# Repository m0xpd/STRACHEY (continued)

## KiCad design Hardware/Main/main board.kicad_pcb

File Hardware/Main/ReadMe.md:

# Main Board

This folder contains details of STRACHEY's Main Board which you seen below (component side) 

<p width=100%, align="center">

You can download the main board's schematic as a [.sch file](https://github.com/m0xpd/STRACHEY/blob/main/Hardware/Main/main%20board.kicad_sch) into your PCB program (KiCad etc) or see a [PDF version](https://github.com/m0xpd/STRACHEY/blob/main/Hardware/Main/main%20board%20schematic.pdf).

The Main Board hosts power supplies, the Arduino Nano, the DACs, output drivers, input protection and conditioning circuits, the Turing Machine Expansion port, and interface to the control Board.

I am new to KiCad and the BoM generator produces output in .csv format. I have decided to save this information [as an Excel file](https://github.com/m0xpd/STRACHEY/blob/main/Hardware/Main/Strachey%20main%20board%20BoM.xlsx) to retain some edits I made. 

There are a few minor points of potential confusion in the BoM (e.g. where I gave some resistors value "10K" and others "10k"), but I'm sure you'll figure it out. Note particularly that the two multi-turn trimmers, TR1 and TR2  (the blue components seen in the photo above) are listed as having value 1k in the schematic and the BoM. I decided to use 10k components,as I had them to hand. Any value above 1k (and up to 100k) will work fine. There is some description of calibrating the trimmers [here](https://github.com/m0xpd/STRACHEY/tree/main#calibration-and-configuration).

I am grateful to 'Harpooneer' who is building a STRACHEY sequencer - he has pointed out that the Main PCB is too congested around the trimmers TR1 and TR2 and we have discussed the build. TR1 and TR2 should be Bourns 3296W (or equivalent) types. They do just fit (as you see in the image above) but it certainly is a squeeze! I found assembly of the prototype easier if you fit the trimmers before other adjacent componenents (R37, R43, R44 and R45) and ensure that C8 is a slim disc ceramic. 

The [.pcb file](https://github.com/m0xpd/STRACHEY/blob/main/Hardware/Main/main%20board.kicad_pcb) and [.pro file](https://github.com/m0xpd/STRACHEY/blob/main/Hardware/Main/main%20board.kicad_pro) (togther with the [.sch file](https://github.com/m0xpd/STRACHEY/blob/main/Hardware/Main/main%20board.kicad_sch) ) constitute a KiCad project, which define the Main board. 

[JLCPCB](https://jlcpcb.com) made the boards for my prototype and did their usual excellent job (usual disclaimer) - you can see the top and bottom sides of the Main Board below:

There is description of how to configure the expansion port (the 2*8 pin header, JP4, seen at the bottom of the main board) by setting shorting links on JP3 (the 3 pin header, near the middle of the main board) [here](https://github.com/m0xpd/STRACHEY/tree/main#calibration-and-configuration).

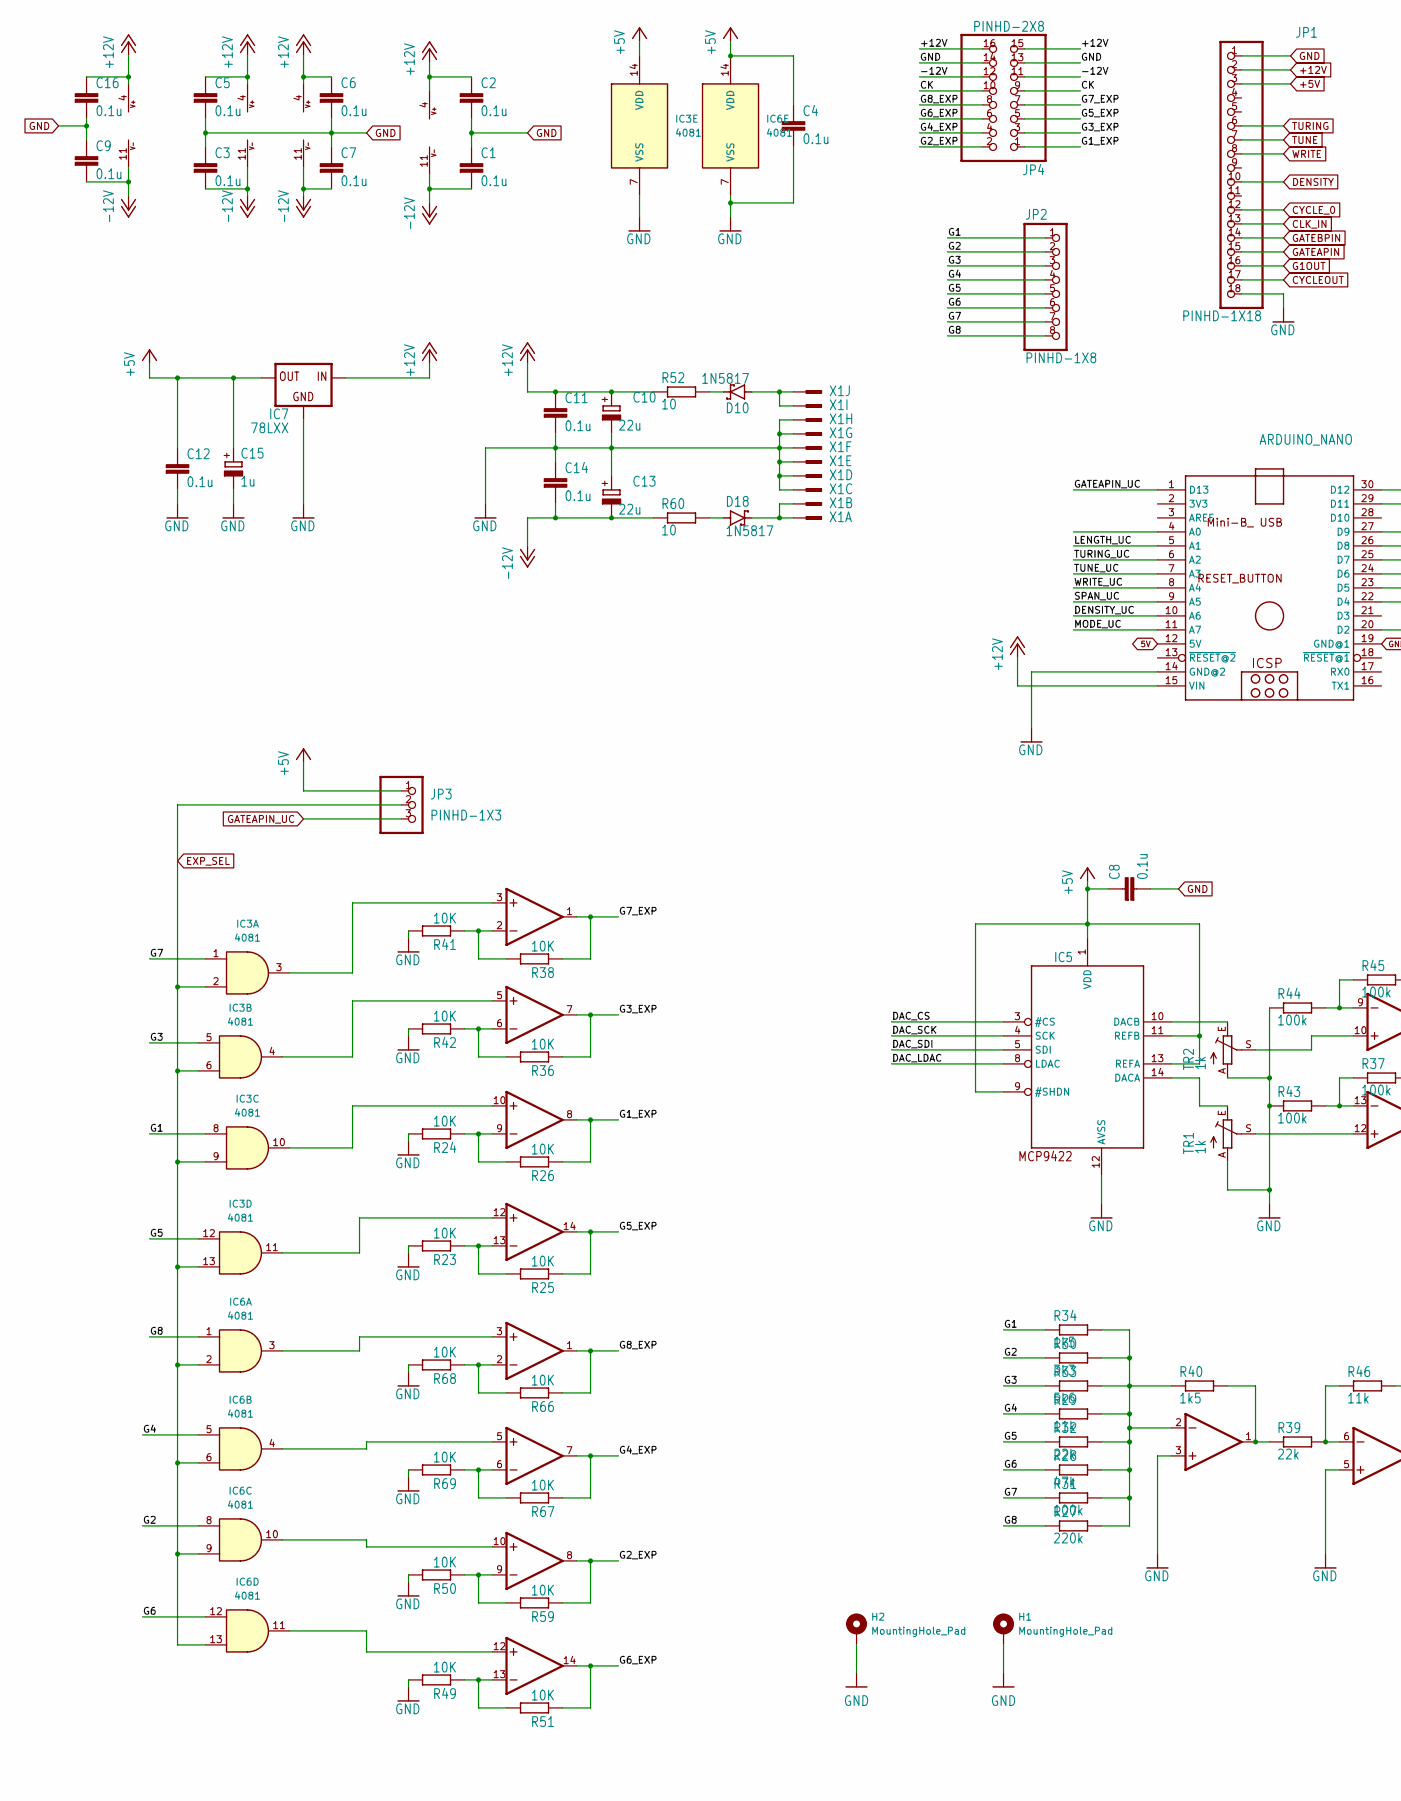
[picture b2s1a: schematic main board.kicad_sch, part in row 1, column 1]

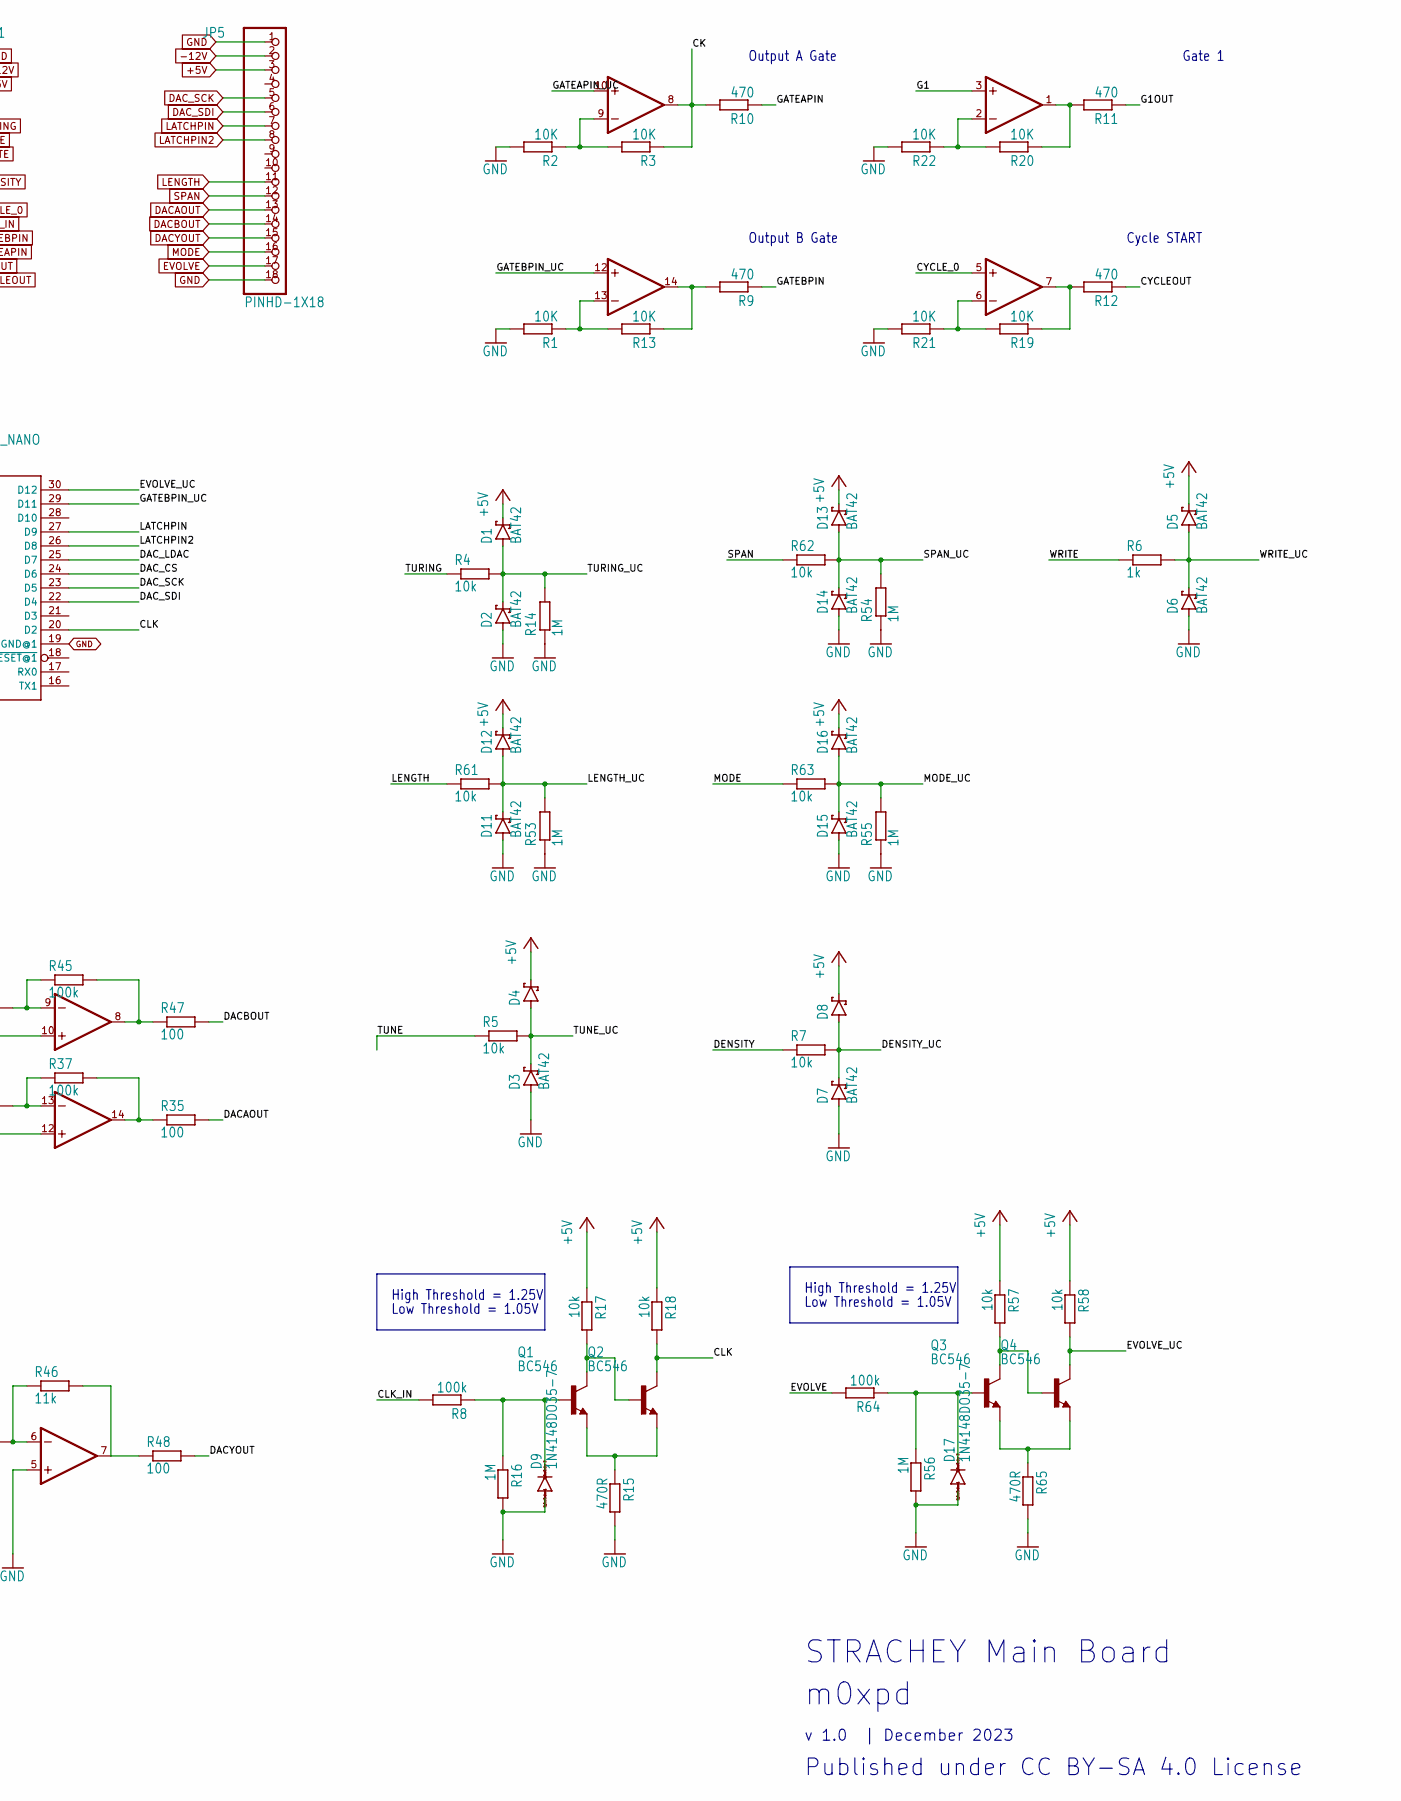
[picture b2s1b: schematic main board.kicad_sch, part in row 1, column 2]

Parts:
C1, C2, C3, C4, C5, C6, C7, C8, C9, C11, C12, C14, C16: 0.1u; C050-025X075
C10, C13: 22u; E2,5-5
C15: 1u; E2,5-5
D1, D2, D3, D4, D5, D6, D7, D8, D11, D12, D13, D14, D15, D16: BAT42; DO35-7
D9, D17: 1N4148DO35-7; DO35-7
D10, D18: 1N5817; DO35-7
H1, H2: MountingHole_Pad; MountingHole_3.2mm_M3_DIN965_Pad_TopBottom
IC1, IC2, IC4, IC8: TL084P; DIL14
IC3, IC6: 4081; DIP-14_W7.62mm_Socket_LongPads
IC5: MCP9422; DIL14
IC7: 78LXX
JP1, JP5: PINHD-1X18; 1X18
JP2: PINHD-1X8; 1X08
JP3: PINHD-1X3; 1X03
JP4: PINHD-2X8; 2X08
Q1, Q2, Q3, Q4: BC546; TO92-EBC
R1, R2, R3, R13, R19, R20, R21, R22, R23, R24, R25, R26, R36, R38, R41, R42, R49, R50, R51, R59, R66, R67, R68, R69: 10K; 0204_7
R4, R5, R7, R17, R18, R57, R58, R61, R62, R63: 10k; 0204_7
R6: 1k; 0204_7
R8, R31, R37, R43, R44, R45, R64: 100k; 0204_7
R9, R10, R11, R12: 470; 0204_7
R14, R16, R53, R54, R55, R56: 1M; 0204_7
R15, R65: 470R; 0204_7
R27: 220k; 0204_7
R28: 47k; 0204_7
R29, R46: 11k; 0204_7
R30: 3k3; 0204_7
R32, R39: 22k; 0204_7
R33: 5k6; 0204_7
R34, R40: 1k5; 0204_7
R35, R47, R48: 100; 0204_7
R52, R60: 10; 0204_7
TR1, TR2: 1k; B64Y
U$1: ARDUINO_NANO
X1: 2510-; PAK100_2500-10

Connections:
5V: U$1.12 (5V)
+5V: C4.1, C8.1, C12.1, C15.+, D1.C, D4.C, D5.C, D8.C, D12.C, D13.C, D16.C, IC3.14 (VDD), IC5.1 (VDD), IC5.9 (#SHDN), IC5.11 (REFB), IC5.13 (REFA), IC6.14 (VDD), IC7.OUT, JP1.3, JP3.1, JP5.3, R17.1, R18.1, R57.1, R58.1
+12V: C2.1, C5.1, C6.1, C10.+, C11.1, C16.1, IC1.4 (V+), IC2.4 (V+), IC4.4 (V+), IC7.IN, IC8.4 (V+), JP1.2, JP4.15, JP4.16, R52.1, U$1.15 (VIN)
-12V: C1.2, C3.2, C7.2, C9.2, C13.-, C14.2, IC1.11 (V-), IC2.11 (V-), IC4.11 (V-), IC8.11 (V-), JP4.11, JP4.12, JP5.2, R60.1
/CK: IC1.8 (OUT), JP4.9, JP4.10, R3.1, R10.2
/CLK: Q2.C, R18.2, U$1.20 (D2)
/DAC_CS: IC5.3 (#CS), U$1.24 (D6)
/DAC_LDAC: IC5.8 (LDAC), U$1.25 (D7)
/DENSITY_UC: D7.C, D8.A, R7.2, U$1.10 (A6)
/EVOLVE_UC: Q4.C, R58.2, U$1.30 (D12)
/G1: IC1.3 (+IN), IC3.8, JP2.1, R34.1
/G1_EXP: IC2.8 (OUT), JP4.1, R26.1
/G2: IC6.8, JP2.2, R30.1
/G2_EXP: IC8.8 (OUT), JP4.2, R59.1
/G3: IC3.5, JP2.3, R33.1
/G3_EXP: IC2.7 (OUT), JP4.3, R36.1
/G4: IC6.5, JP2.4, R29.1
/G4_EXP: IC8.7 (OUT), JP4.4, R67.1
/G5: IC3.12, JP2.5, R32.1
/G5_EXP: IC2.14 (OUT), JP4.5, R25.1
/G6: IC6.12, JP2.6, R28.1
/G6_EXP: IC8.14 (OUT), JP4.6, R51.1
/G7: IC3.1, JP2.7, R31.1
/G7_EXP: IC2.1 (OUT), JP4.7, R38.1
/G8: IC6.1, JP2.8, R27.1
/G8_EXP: IC8.1 (OUT), JP4.8, R66.1
/GATEBPIN_UC: IC1.12 (+IN), U$1.29 (D11)
/LENGTH_UC: D11.C, D12.A, R53.2, R61.2, U$1.5 (A1)
/MODE_UC: D15.C, D16.A, R55.2, R63.2, U$1.11 (A7)
/SPAN_UC: D13.A, D14.C, R54.2, R62.2, U$1.9 (A5)
/TUNE_UC: D3.C, D4.A, R5.2, U$1.7 (A3)
/TURING_UC: D1.A, D2.C, R4.2, R14.2, U$1.6 (A2)
/WRITE_UC: D5.A, D6.C, R6.2, U$1.8 (A4)
CLK_IN: JP1.13, R8.2
CYCLEOUT: JP1.17, R12.1
CYCLE_0: IC1.5 (+IN), JP1.12
DACAOUT: JP5.13, R35.2
DACBOUT: JP5.14, R47.2
DACYOUT: JP5.15, R48.2
DAC_SCK: IC5.4 (SCK), JP5.5, U$1.23 (D5)
DAC_SDI: IC5.5 (SDI), JP5.6, U$1.22 (D4)
DENSITY: JP1.10, R7.1
EVOLVE: JP5.17, R64.2
EXP_SEL: IC3.2, IC3.6, IC3.9, IC3.13, IC6.2, IC6.6, IC6.9, IC6.13, JP3.2
G1OUT: JP1.16, R11.1
GATEAPIN: JP1.15, R10.1
GATEAPIN_UC: IC1.10 (+IN), JP3.3, U$1.1 (D13)
GATEBPIN: JP1.14, R9.1
GND: C1.1, C2.2, C3.1, C4.2, C5.2, C6.2, C7.1, C8.2, C9.1, C10.-, C11.2, C12.2, C13.+, C14.1, C15.-, C16.2, D2.A, D3.A, D6.A, D7.A, D9.A, D11.A, D14.A, D15.A, D17.A, H1.1, H2.1, IC3.7 (VSS), IC4.3 (+IN), IC4.5 (+IN), IC5.12 (AVSS), IC6.7 (VSS), IC7.GND, JP1.1, JP1.18, JP4.13, JP4.14, JP5.1, JP5.18, R1.2, R2.2, R14.1, R15.2, R16.2, R21.2, R22.2, R23.2, R24.2, R41.2, R42.2, R43.1, R44.1, R49.2, R50.2, R53.1, R54.1, R55.1, R56.2, R65.2, R68.2, R69.2, TR1.A, TR2.A, U$1.14 (GND@2), U$1.19 (GND@1), X1.3 (KL), X1.4 (KL), X1.5 (KL), X1.6 (KL), X1.7 (KL), X1.8 (KL)
LATCHPIN: JP5.7, U$1.27 (D9)
LATCHPIN2: JP5.8, U$1.26 (D8)
LENGTH: JP5.11, R61.1
MODE: JP5.16, R63.1
unnamed: D9.C, Q1.B, R8.1, R16.1
unnamed: D17.C, Q3.B, R56.1, R64.1
unnamed: D10.C, R52.2
unnamed: D18.A, R60.2
unnamed: IC6.3, IC8.3 (+IN)
unnamed: IC8.2 (-IN), R66.2, R68.1
unnamed: IC6.4, IC8.5 (+IN)
unnamed: IC8.6 (-IN), R67.2, R69.1
unnamed: IC6.10, IC8.10 (+IN)
unnamed: IC8.9 (-IN), R50.1, R59.2
unnamed: IC6.11, IC8.12 (+IN)
unnamed: IC8.13 (-IN), R49.1, R51.2
unnamed: IC5.14 (DACA), TR1.E
unnamed: IC5.10 (DACB), TR2.E
unnamed: IC4.2 (-IN), R27.2, R28.2, R29.2, R30.2, R31.2, R32.2, R33.2, R34.2, R40.1
unnamed: IC4.1 (OUT), R39.1, R40.2
unnamed: IC4.6 (-IN), R39.2, R46.1
unnamed: IC4.7 (OUT), R46.2, R48.1
unnamed: IC4.10 (+IN), TR2.S
unnamed: IC4.9 (-IN), R44.2, R45.1
unnamed: IC4.8 (OUT), R45.2, R47.1
unnamed: IC4.12 (+IN), TR1.S
unnamed: IC4.13 (-IN), R37.1, R43.2
unnamed: IC4.14 (OUT), R35.1, R37.2
unnamed: IC2.3 (+IN), IC3.3
unnamed: IC2.2 (-IN), R38.2, R41.1
unnamed: IC2.5 (+IN), IC3.4
unnamed: IC2.6 (-IN), R36.2, R42.1
unnamed: IC2.10 (+IN), IC3.10
unnamed: IC2.9 (-IN), R24.1, R26.2
unnamed: IC2.12 (+IN), IC3.11
unnamed: IC2.13 (-IN), R23.1, R25.2
unnamed: IC1.2 (-IN), R20.2, R22.1
unnamed: IC1.1 (OUT), R11.2, R20.1
unnamed: IC1.6 (-IN), R19.2, R21.1
unnamed: IC1.7 (OUT), R12.2, R19.1
unnamed: IC1.9 (-IN), R2.1, R3.2
unnamed: IC1.13 (-IN), R1.1, R13.2
unnamed: IC1.14 (OUT), R9.2, R13.1
unnamed: Q1.C, Q2.B, R17.2
unnamed: Q1.E, Q2.E, R15.1
unnamed: Q3.C, Q4.B, R57.2
unnamed: Q3.E, Q4.E, R65.1
unnamed: D18.C, X1.1 (KL), X1.2 (KL)
unnamed: D10.A, X1.9 (KL), X1.10 (KL)
SPAN: JP5.12, R62.1
TUNE: JP1.7, R5.1
TURING: JP1.6, R4.1
WRITE: JP1.8, R6.1

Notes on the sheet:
v 1.0 | December 2023
Gate 1
m0xpd
STRACHEY Main Board
Published under CC BY-SA 4.0 License
Low Threshold = 1.05V
High Threshold = 1.25V
Output B Gate
Output A Gate
Cycle START

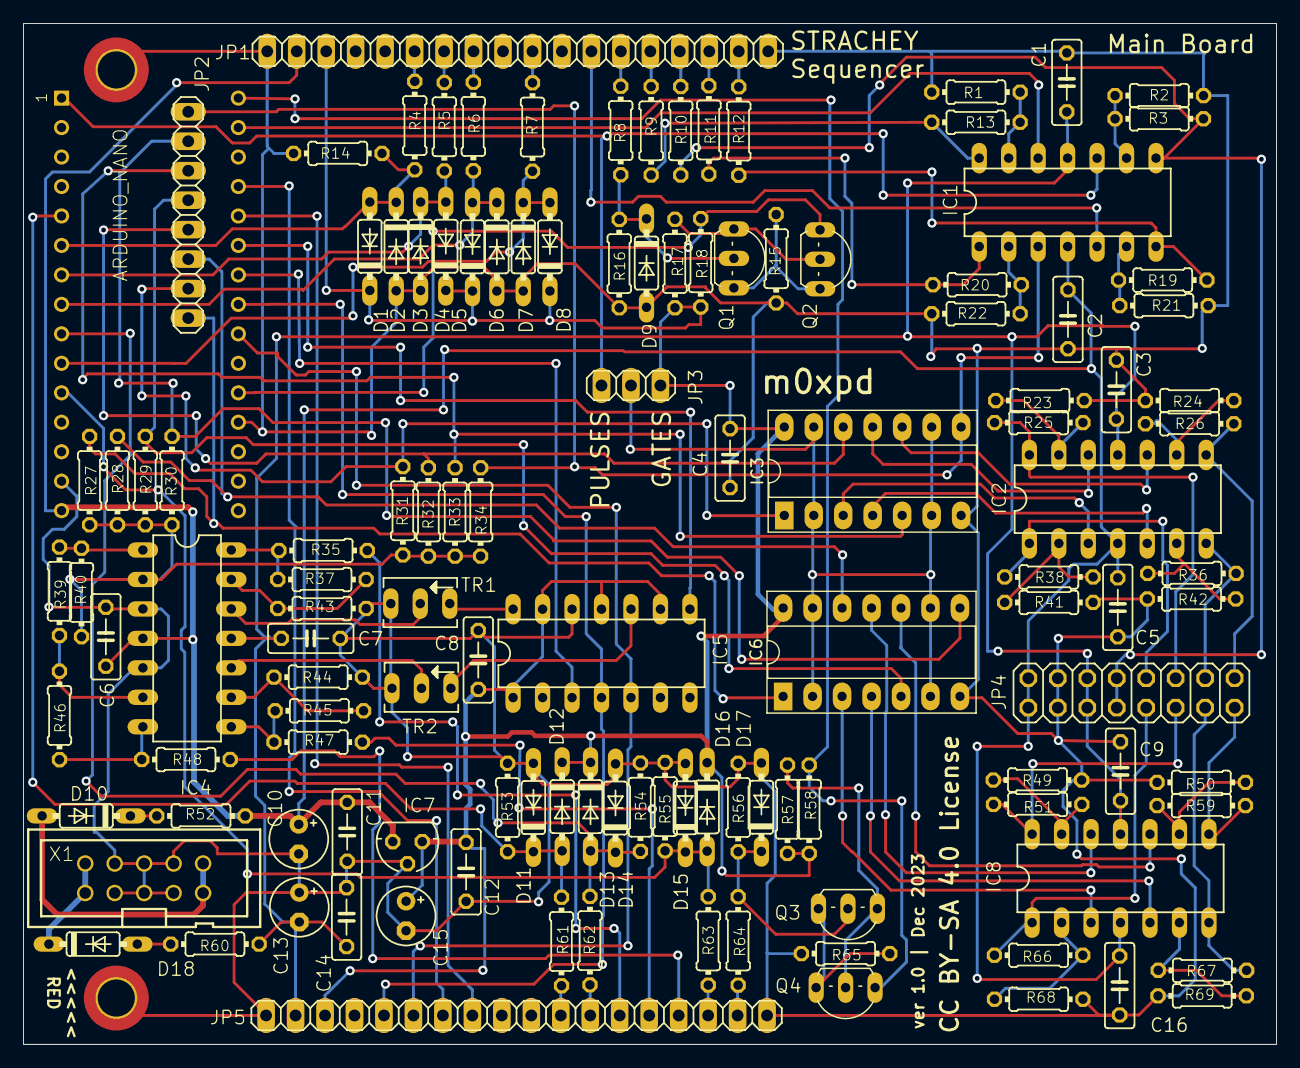
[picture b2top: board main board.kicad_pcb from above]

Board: 2 copper layers, 108.0 x 88.0 mm, 126 parts (0 on the bottom side), 101 nets.

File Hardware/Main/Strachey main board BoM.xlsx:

Source: | xxx
Date: | xxx
Tool: | Eeschema 7.0.9
Generator: | /Applications/KiCad/KiCad.app/Contents/SharedSupport/plugins/bom_csv_grouped_by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
Component Count: | 126
Collated Components:
Item | Qty | Reference(s) | Value |  | LibPart | Footprint | Datasheet | DNP
1 | 13 | C1, C2, C3, C4, C5, C6, C7, C8, C9, C11, C12, C14, C16 | 0.1u |  | main board-eagle-import:C-EU050-025X075 | main board:C050-025X075
2 | 2 | C10, C13 | 22u |  | main board-eagle-import:CPOL-EUE2.5-5 | main board:E2,5-5
3 | 1 | C15 | 1u |  | main board-eagle-import:CPOL-EUE2.5-5 | main board:E2,5-5
4 | 14 | D1, D2, D3, D4, D5, D6, D7, D8, D11, D12, D13, D14, D15, D16 | BAT42 |  | main board-eagle-import:BAT42 | main board:DO35-7
5 | 2 | D9, D17 | 1N4148DO35-7 |  | main board-eagle-import:1N4148DO35-7 | main board:DO35-7
6 | 2 | D10, D18 | 1N5817 | Could be BAT42s as well | main board-eagle-import:SCHOTTKY-DIODEDO35-7 | main board:DO35-7
7 | 2 | H1, H2 | MountingHole_Pad |  | Mechanical:MountingHole_Pad | MountingHole:MountingHole_3.2mm_M3_DIN965_Pad_TopBottom | ~
8 | 4 | IC1, IC2, IC4, IC8 | TL084P |  | main board-eagle-import:TL084P | main board:DIL14
9 | 2 | IC3, IC6 | CD4081 |  | 4xxx:4081 | Package_DIP:DIP-14_W7.62mm_Socket_LongPads | http://www.intersil.com/content/dam/Intersil/documents/cd40/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
10 | 1 | IC5 | MCP9422 |  | main board-eagle-import:MCP9422 | main board:DIL14
11 | 1 | IC7 | 78L05 |  | main board-eagle-import:78LXX | main board:78LXX
12 | 2 | JP1, JP5 | PINHD-1X18 | 1*18 Male 0.1 inch Header | main board-eagle-import:PINHD-1X18 | main board:1X18
13 | 1 | JP2 | PINHD-1X8 | 1*8 Male 0.1 inch header | main board-eagle-import:PINHD-1X8 | main board:1X08
14 | 1 | JP3 | PINHD-1X3 | 1*3 Male 0.1 inch Header | main board-eagle-import:PINHD-1X3 | main board:1X03
15 | 1 | JP4 | PINHD-2X8 | 2*8 Male 0.1 inch Male Header | main board-eagle-import:PINHD-2X8 | main board:2X08
16 | 4 | Q1, Q2, Q3, Q4 | BC546 |  | main board-eagle-import:BC546 | main board:TO92-EBC
17 | 24 | R1, R2, R3, R13, R19, R20, R21, R22, R23, R24, R25, R26, R36, R38, R41, R42, R4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 | 10K |  | main board-eagle-import:R-EU_0204/7 | main board:0204_7
18 | 10 | R4, R5, R7, R17, R18, R57, R58, R61, R62, R63 | 10k |  | main board-eagle-import:R-EU_0204/7 | main board:0204_7
19 | 1 | R6 | 1k |  | main board-eagle-import:R-EU_0204/7 | main board:0204_7
20 | 7 | R8, R31, R37, R43, R44, R45, R64 | 100k |  | main board-eagle-import:R-EU_0204/7 | main board:0204_7
21 | 4 | R9, R10, R11, R12 | 470 |  | main board-eagle-import:R-EU_0204/7 | main board:0204_7
22 | 6 | R14, R16, R53, R54, R55, R56 | 1M |  | main board-eagle-import:R-EU_0204/7 | main board:0204_7
23 | 2 | R15, R65 | 470R |  | main board-eagle-import:R-EU_0204/7 | main board:0204_7
24 | 1 | R27 | 220k |  | main board-eagle-import:R-EU_0204/7 | main board:0204_7
25 | 1 | R28 | 47k |  | main board-eagle-import:R-EU_0204/7 | main board:0204_7
26 | 2 | R29, R46 | 11k |  | main board-eagle-import:R-EU_0204/7 | main board:0204_7
27 | 1 | R30 | 3k3 |  | main board-eagle-import:R-EU_0204/7 | main board:0204_7
28 | 2 | R32, R39 | 22k |  | main board-eagle-import:R-EU_0204/7 | main board:0204_7
29 | 1 | R33 | 5k6 |  | main board-eagle-import:R-EU_0204/7 | main board:0204_7
30 | 2 | R34, R40 | 1k5 |  | main board-eagle-import:R-EU_0204/7 | main board:0204_7
31 | 3 | R35, R47, R48 | 100 |  | main board-eagle-import:R-EU_0204/7 | main board:0204_7
32 | 2 | R52, R60 | 10 |  | main board-eagle-import:R-EU_0204/7 | main board:0204_7
33 | 2 | TR1, TR2 | 1k | This is a min value - I used 10k Trimmers | main board-eagle-import:TRIM_EU-B64Y | main board:B64Y
34 | 1 | U$1 | ARDUINO_NANO |  | main board-eagle-import:ARDUINO_NANOARDUINO_NANO | main board:ARDUINO_NANO
35 | 1 | X1 | Power Header | 2*10 0.1 inch walled Header | main board-eagle-import:2510- | main board:PAK100_2500-10

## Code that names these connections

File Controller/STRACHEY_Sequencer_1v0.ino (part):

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int semitoneA = 0;
int semitoneB = 0;
int Offset = 0;
int Density = 0;
int oldDensity = 0;
int Turing = 0;   // Main Turing Control Knob Value
int TuringCurve = 0; // non-linear operation on the Turing Input
int Tune = 0;     // Slider Tuning
int oldTune = 0;  // Previous Slider Tuning
int Write = 0;    // Write Switch value
int Span = 0;     // Octave Span value;
int oldSpan = 0;  // old value of Span;
int oldseqLength = 0;
int TuneDisplay = 0;
int TuneDisplay2 = 0;
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int stroke = 1;

// Arduino pin allocations...
const int CLK_IN = 2;
const int  DAC_SDI = 4;         // MCP4922...
const int  DAC_SCK = 5;
const int  DAC_CS = 6;
const int  DAC_LDAC = 7;
const int latchPin2 = 8;        //Pin connected to SH_CP of second 74HC595 (pin 12)
const int latchPin = 9;         //Pin connected to SH_CP of 74HC595 (pin 12)
const int gateBPin = 11;
const int modePin = 12;          // INPUT for CHANGE call inputs
const int gateAPin = 13;

const int LengthKnob = 1;        // ANALOG INPUT for LENGTH Control
const int TuringKnob = 2;        // ANALOG INPUT for main TURING Machine Control
const int TuneKnob = 3;          // ANALOG INPUT for Weights TUNING Selection
const int WriteSwitch = 4;       // ANALOG INPUT for Write Switch Input
const int SpanKnob = 5;          // ANALOG INPUT for Octave SPAN input
const int DensityKnob = 6;       // ANALOG INPUT for Euclidean DENSITY input
const int ModeKnob = 7;          // ANALOG INPUT for weight change 'METHOD' inputs


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  setupHardware();
  randomSeed(millis());
  gateDisplay = 0;
  digitalWrite(latchPin, LOW);
  shiftOut(DAC_SDI, DAC_SCK, MSBFIRST, gateDisplay);
  digitalWrite(latchPin, HIGH);
  write_Tune_Display();
  seqLength = 2 + (analogRead(LengthKnob) / 72);
  if (seqLength < 2) {
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  bool Bplay = bitRead(euclidPattern, CycleNo);       // Is there an onset in the Euclidean pattern at this point (Bplay=true)?
  if (Bplay) {                                        // do we have to play channel B on this step?
    Set_DAC_B(semitoneB * StepsPerSemitone);          // if yes, set the DAC channel
    digitalWrite(gateBPin, HIGH);
  }
  digitalWrite(gateAPin, HIGH);
  while (digitalRead(CLK_IN) == 1) {                  // wait until the end of the clock HIGH phase, reading the WRITE switch
    Write = analogRead(WriteSwitch);
  }
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    ChangeFlag = true;
  }

  digitalWrite(gateAPin, LOW);
  digitalWrite(gateBPin, LOW);
  // =============================================================================
  // This is the MAIN PART of the SOFTWARE IMPLEMENTATION OF THE TURING MACHINE...
  // ============================================================================= 
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  for (int i = 0; i < 8; i++) {
    gateDisplay = gateDisplay + (gates[i] << i);
  }
  digitalWrite(latchPin, LOW);
  shiftOut(DAC_SDI, DAC_SCK, MSBFIRST, gateDisplay);
  digitalWrite(latchPin, HIGH);
}

void write_Tune_Display(){
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
  int wTuneDisplay2 = TuneDisplay2 | mode << 3;
  wTuneDisplay2 = wTuneDisplay2 | highTuneDisplay;
  digitalWrite(latchPin2, LOW);
  shiftOut(DAC_SDI, DAC_SCK, MSBFIRST, wTuneDisplay2);
  shiftOut(DAC_SDI, DAC_SCK, MSBFIRST, TuneDisplay);
  digitalWrite(latchPin2, HIGH);
}

void write_Tune_Display_ModeOFF()
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  TuneDisplay = 1 << lowTune;
  int wTuneDisplay2 = TuneDisplay2 | (0) << 3;
  wTuneDisplay2 = wTuneDisplay2 | highTuneDisplay;
  digitalWrite(latchPin2, LOW);
  shiftOut(DAC_SDI, DAC_SCK, MSBFIRST, wTuneDisplay2);
  shiftOut(DAC_SDI, DAC_SCK, MSBFIRST, TuneDisplay);
  digitalWrite(latchPin2, HIGH);
}


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
void setupHardware() {
  // temporary 595 setup...
  pinMode(latchPin, OUTPUT);
  pinMode(latchPin2, OUTPUT);
  // end of temp 595 setup

  // DAC Setup...
  pinMode(DAC_CS, OUTPUT);
  pinMode(DAC_SCK, OUTPUT);
  pinMode(DAC_SDI, OUTPUT);
  pinMode(DAC_LDAC, OUTPUT);
  // Gates...
  pinMode(gateAPin, OUTPUT);
  pinMode(gateBPin, OUTPUT);
  pinMode(modePin, INPUT_PULLUP);
  pinMode(CLK_IN, INPUT);
  // Initialise outputs...
  digitalWrite(DAC_CS, HIGH);
  digitalWrite(DAC_LDAC, HIGH);
  digitalWrite(DAC_SCK, LOW);
  digitalWrite(DAC_SDI, HIGH);
  digitalWrite(gateAPin, LOW);
  digitalWrite(gateBPin, LOW);
}

// ================================================================================
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// Function to find the binary length of a number by counting bitwise
int findlength(unsigned int bnry) {
  boolean lengthfound = false;
  int length = 1; // no number can have a length of zero - single 0 has a length of one, but no 1s for the sytem to count
  for (int q = 32; q >= 0; q--) {
    int r = bitRead(bnry, q);
    if (r == 1 && lengthfound == false) {
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
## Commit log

2023-11-30 Rename README.txt to Hardware/README.txt
2023-11-30 Rename README.txt to README.md
2023-11-30 Rename README.txt to Controller/README.txt
2023-12-10 Rename Controller/STRACHEY_Sequencer_1v0.ino to Controller/Code/STRACHEY_Sequencer_1v0.ino
2023-12-10 Rename Hardware/README.txt to Hardware/Graphics/README.txt
2023-12-12 Rename Hardware/main board schematic.pdf to Hardware/Main/main board schematic.pdf
2023-12-12 Rename Hardware/Main/Main Board Schematic.jpg to Hardware/Main/Graphics/Main Board Schematic.jpg
2023-12-12 Rename Hardware/Main/STRACHEY Main Board Component Side Populated.jpg to Hardware/Main/Graphics/STRACHEY Main Board Component Side Populated.jpg
2023-12-12 Rename Hardware/Control/STRACHEY Control Board Component Side Populated.jpg to Hardware/Control/Graphics/STRACHEY Control Board Component Side Populated.jpg
